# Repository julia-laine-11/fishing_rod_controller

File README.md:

# fishing_rod_controller
This was part of an EPICS team project for an automatically casting and reeling fishing rod. I designed this PCB for the controller so it would stop falling apart during travel and use.

Our project partner was a [kid named Colton in Indianapolis](https://www.facebook.com/ColtonsQuest/) who has AMC. He likes to fish but he cannot hold the fishing rod. Our team designed an automatically casting and reeling fishing rod to help him out.

I took lead of the electronics on the team and I created this PCB:

*top view*

*bottom view*

*schematic*

## Pictures of use and design:

*the initial design tested on a breadboard*

*the first PCB design - I forgot to add thru holes to connect the ground planes*

*the second PCB design. I made more changes as I learned from my first design. Notice the larger isolation and more options for alternate parts.*

*my teammates on the left, our project partner, Colton, on the right*

[Here is a video](https://www.facebook.com/reel/425838616804608) of Colton using it.

[And another](https://www.facebook.com/share/v/JBNppNtS4n77EEXA/)

*Colton and a fish he caught with the fishing rod*

*our team and Colton*

## Controller housing

*The lid is seperate and there are 3 buttons on the top. The controller housing is a triangle shape so Colton can easily hold it between his legs.*

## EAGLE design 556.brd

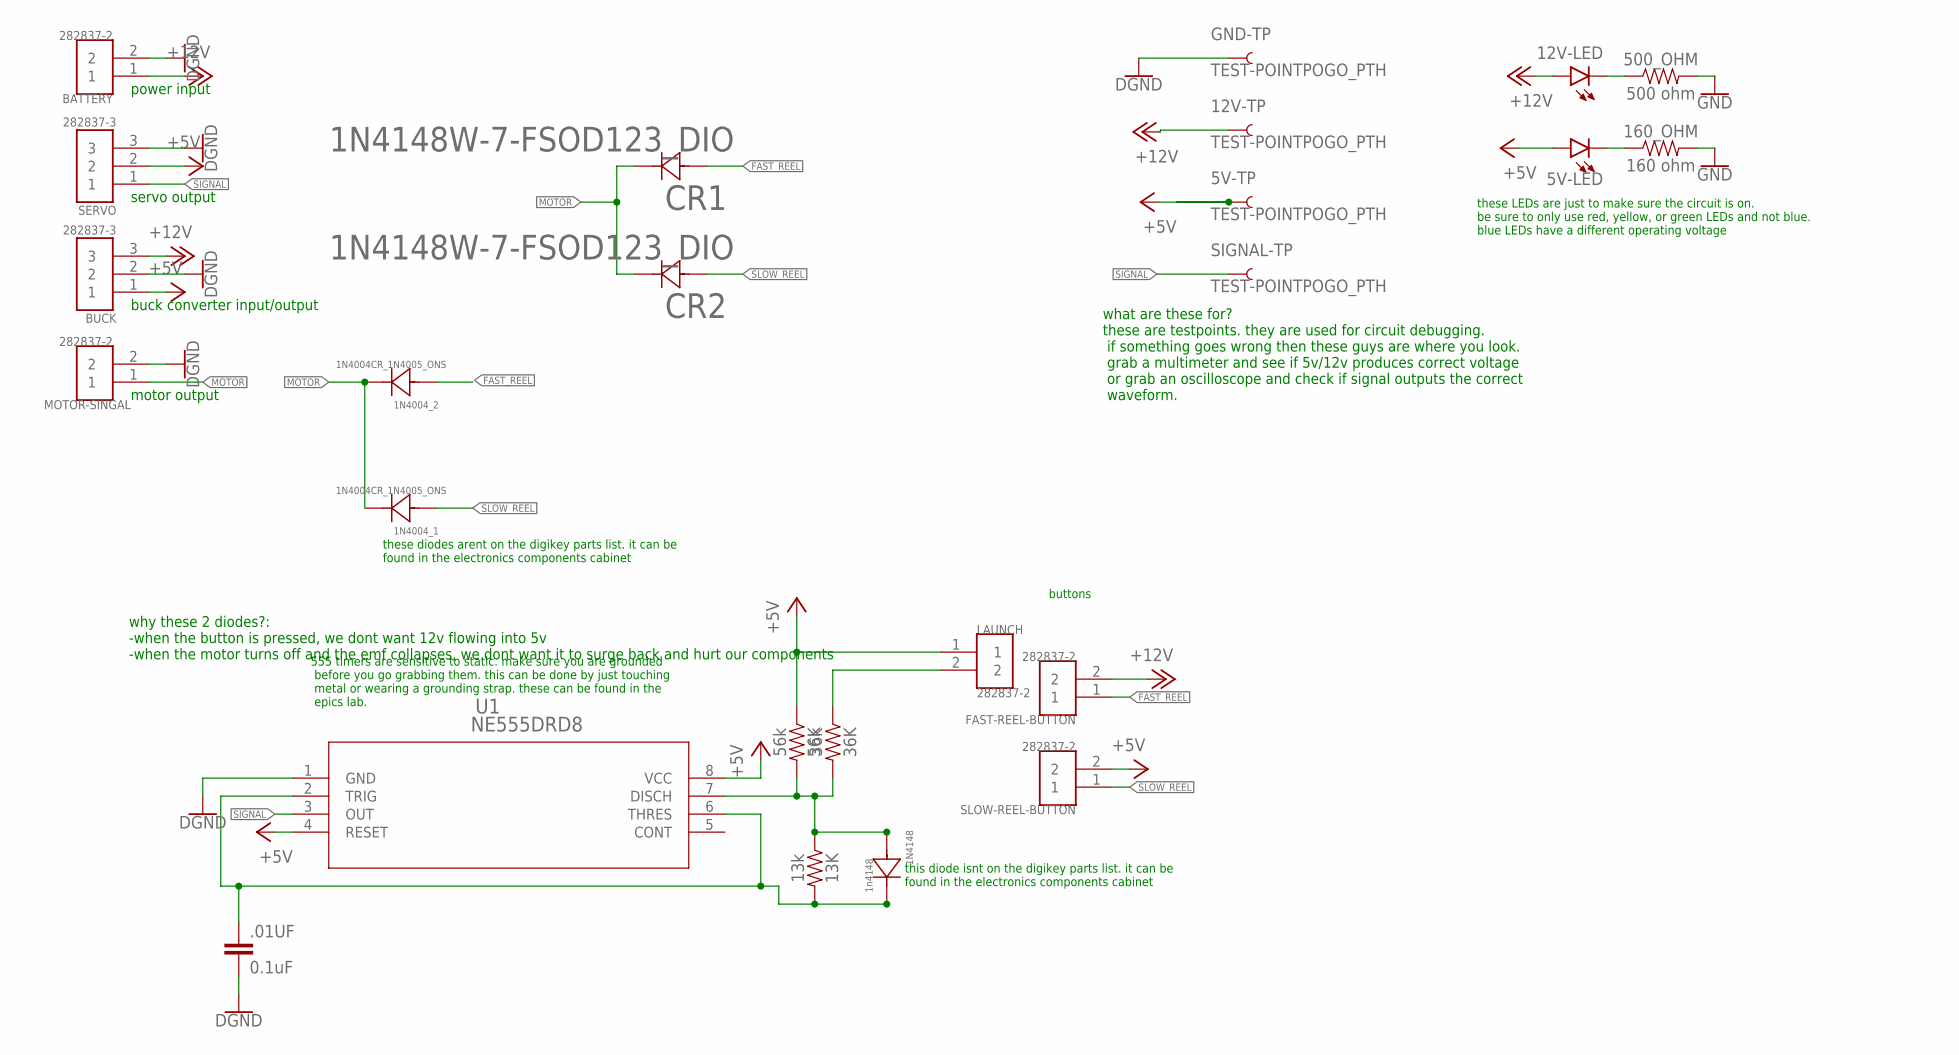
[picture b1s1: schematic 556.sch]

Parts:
1N4004_1, 1N4004_2: 1N4004CR_1N4005_ONS; CR_1N4005_ONS
1N4148: 1n4148; CR_1N4005_ONS
5V-LED, 12V-LED: LED0603; LED-0603
5V-TP, 12V-TP: TEST-POINTPOGO_PTH; 1X01_NO_SILK
13K: 13k; 0603
36K: 36k; 0603
56K: 56k; 0603
160_OHM: 160 ohm; 0603
500_OHM: 500 ohm; 0603
.01UF: 0.1uF; 0402-CAP
BATTERY: 282837-2; TE_282837-2
BUCK: 282837-3; TE_282837-3
CR1, CR2: 1N4148W-7-FSOD123_DIO; SOD123_DIO
FAST-REEL-BUTTON: 282837-2; TE_282837-2
GND-TP: TEST-POINTPOGO_PTH; 1X01_NO_SILK
LAUNCH: 282837-2; TE_282837-2
MOTOR-SINGAL: 282837-2; TE_282837-2
SERVO: 282837-3; TE_282837-3
SIGNAL-TP: TEST-POINTPOGO_PTH; 1X01_NO_SILK
SLOW-REEL-BUTTON: 282837-2; TE_282837-2
U1: NE555DRD8; D8

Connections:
+5V: 5V-LED.A, 5V-TP.1, 56K.1, BUCK.1, LAUNCH.1, SERVO.2, SLOW-REEL-BUTTON.2, U1.4 (RESET), U1.8 (VCC)
+12V: 12V-LED.A, 12V-TP.1, BATTERY.1, BUCK.3, FAST-REEL-BUTTON.2
FAST_REEL: 1N4004_2.2, CR1.2, FAST-REEL-BUTTON.1
GND: 160_OHM.2, 500_OHM.2, .01UF.2, BATTERY.2, BUCK.2, GND-TP.1, MOTOR-SINGAL.2, SERVO.3, U1.1 (GND)
MOTOR: 1N4004_1.1, 1N4004_2.1, CR1.1, CR2.1, MOTOR-SINGAL.1
unnamed: 36K.1, LAUNCH.2
unnamed: 1N4148.1, 13K.2, .01UF.1, U1.2 (TRIG), U1.6 (THRES)
unnamed: 1N4148.2, 13K.1, 36K.2, 56K.2, U1.7 (DISCH)
unnamed: 5V-LED.C, 160_OHM.1
unnamed: 12V-LED.C, 500_OHM.1
SIGNAL: SERVO.1, SIGNAL-TP.1, U1.3 (OUT)
SLOW_REEL: 1N4004_1.2, CR2.2, SLOW-REEL-BUTTON.1

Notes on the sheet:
why these 2 diodes?: -when the button is pressed, we dont want 12v flowing into 5v -when the motor turns off and the emf collapses, we dont want it to surge back and hurt our components
power input
servo output
buck converter input/output
motor output
what are these for? these are testpoints. they are used for circuit debugging. if something goes wrong then these guys are where you look. grab a multimeter and see if 5v/12v produces correct voltage or grab an oscilloscope and check if signal outputs the correct waveform.
these LEDs are just to make sure the circuit is on. be sure to only use red, yellow, or green LEDs and not blue. blue LEDs have a different operating voltage
555 timers are sensitive to static. make sure you are grounded before you go grabbing them. this can be done by just touching metal or wearing a grounding strap. these can be found in the epics lab.
this diode isnt on the digikey parts list. it can be found in the electronics components cabinet
these diodes arent on the digikey parts list. it can be found in the electronics components cabinet
buttons

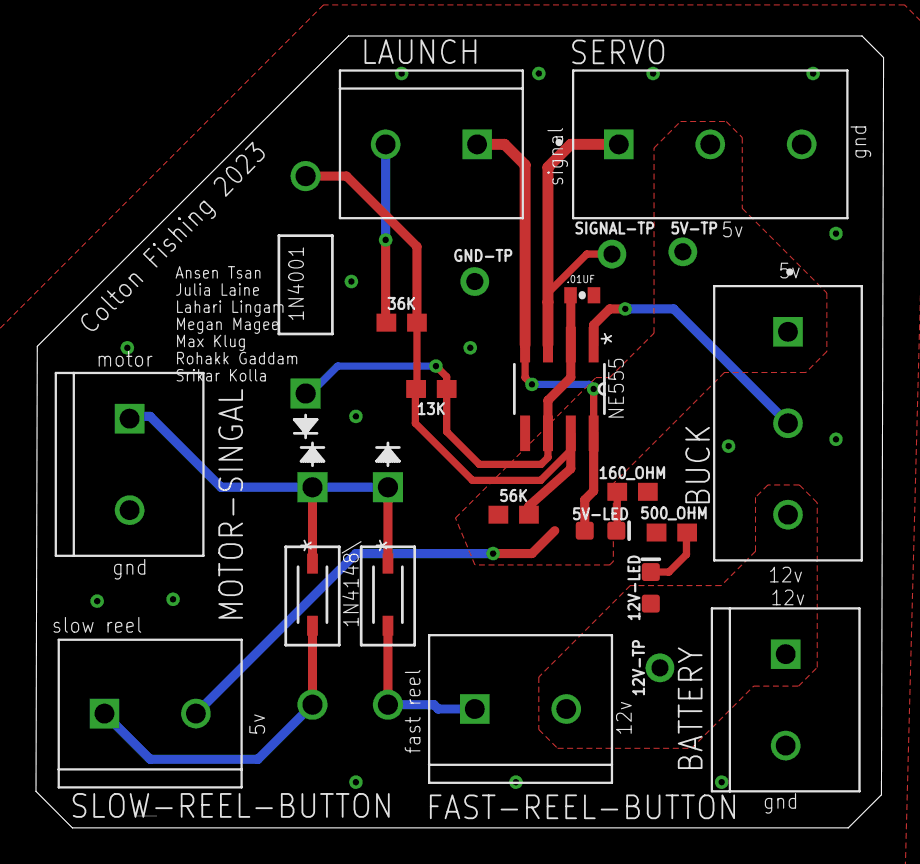
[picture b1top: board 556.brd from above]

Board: 2 copper layers, 47.1 x 44.0 mm, 25 parts (0 on the bottom side), 12 nets.

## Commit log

2024-11-14 Update README.md
    i made a typo lol

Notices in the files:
parts and their libraries:
SparkFun-Resistors: Licensing: Creative Commons ShareAlike 4.0 International - https://creativecommons.org/licenses/by-sa/4.0
COPYRIGHT: Copyright (C) 2023 Ultra Librarian. All rights reserved.
